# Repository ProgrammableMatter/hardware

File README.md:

Particle Hardware Repository
----------------------------
Hardware development repository for the particle and related hardware.

## Folder content
* **pcb-projects**: pcb projects
* **freecad**: 3D Models drawn with [FreeCAD](http://www.freecadweb.org/)
* **reflow**: reflow soldering logs, charts and helper

## PCB Projects/Versions
### Particle Version 1.21
|   |   |   |
|---|---|---|
|  |  |  |
| plugable particle with leads | pluggable particle | grid board illustartion |

### Particle version 1.1

|   |   |   | 
|---|---|---|
||||
| single particle | array example | array header |
|  | | | 
| array tail | | |

### Particle version 0.9
|   |
|---|
||
| chain example |

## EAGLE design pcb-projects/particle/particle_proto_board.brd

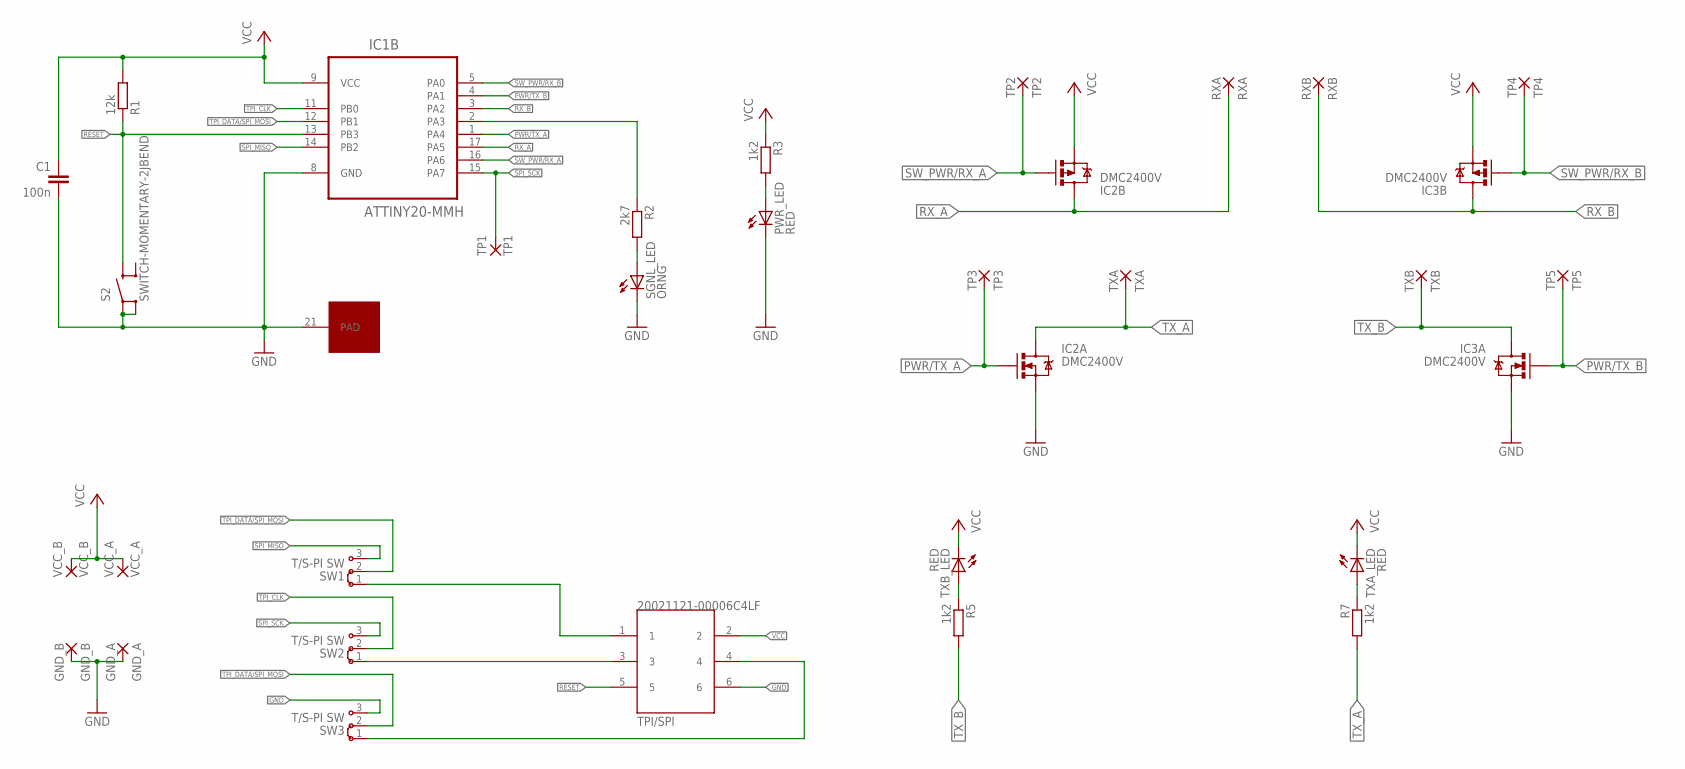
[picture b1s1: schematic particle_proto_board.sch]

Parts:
C1: 100n; C1206
GND_A: GND_A; 1,6/0,9
GND_B: GND_B; 1,6/0,9
IC1: ATTINY20-MMH; QFN45P300X300X85-21N
IC2, IC3: DMC2400V; SOT563
PWR_LED: RED; SML1206
R1: 12k; R1206
R2: 2k7; R1206
R3, R5, R7: 1k2; R1206
RXA: RXA; 1,6/0,9
RXB: RXB; 1,6/0,9
S2: SWITCH-MOMENTARY-2JBEND; KSC351JLFS
SGNL_LED: ORNG; SML1206
SW1, SW2, SW3: T/S-PI SW; 04C
TP1: TP1; 1,6/0,9
TP2: TP2; 1,6/0,9
TP3: TP3; 1,6/0,9
TP4: TP4; 1,6/0,9
TP5: TP5; 1,6/0,9
TPI/SPI: 20021121-00006C4LF
TXA: TXA; 1,6/0,9
TXA_LED: RED; SML1206
TXB: TXB; 1,6/0,9
TXB_LED: RED; SML1206
VCC_A: VCC_A; 1,6/0,9
VCC_B: VCC_B; 1,6/0,9

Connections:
GND: C1.2, GND_A.1, GND_B.1, IC1.8 (GND), IC1.21 (PAD), IC2.1 (S), IC3.1 (S), PWR_LED.C, S2.1@1 (1), S2.1@2 (1), SGNL_LED.C, SW3.3, TPI/SPI.6
unnamed: SW1.1, TPI/SPI.1
unnamed: SW3.1, TPI/SPI.4
unnamed: R7.1, TXA_LED.A
unnamed: SW2.1, TPI/SPI.3
unnamed: R5.1, TXB_LED.A
unnamed: R2.2, SGNL_LED.A
unnamed: PWR_LED.A, R3.2
unnamed: IC1.2 (PA3), R2.1
PWR/TX_A: IC1.1 (PA4), IC2.2 (G), TP3.1
PWR/TX_B: IC1.4 (PA1), IC3.2 (G), TP5.1
RESET: IC1.13 (PB3), R1.1, S2.2@1 (2), TPI/SPI.5
RX_A: IC1.17 (PA5), IC2.3 (D), RXA.1
RX_B: IC1.3 (PA2), IC3.3 (D), RXB.1
SPI_MISO: IC1.14 (PB2), SW1.3
SPI_SCK: IC1.15 (PA7), SW2.3, TP1.1
SW_PWR/RX_A: IC1.16 (PA6), IC2.5 (G), TP2.1
SW_PWR/RX_B: IC1.5 (PA0), IC3.5 (G), TP4.1
TPI_CLK: IC1.11 (PB0), SW2.2
TPI_DATA/SPI_MOSI: IC1.12 (PB1), SW1.2, SW3.2
TX_A: IC2.6 (D), R7.2, TXA.1
TX_B: IC3.6 (D), R5.2, TXB.1
VCC: C1.1, IC1.9 (VCC), IC2.4 (S), IC3.4 (S), R1.2, R3.1, TPI/SPI.2, TXA_LED.C, TXB_LED.C, VCC_A.1, VCC_B.1

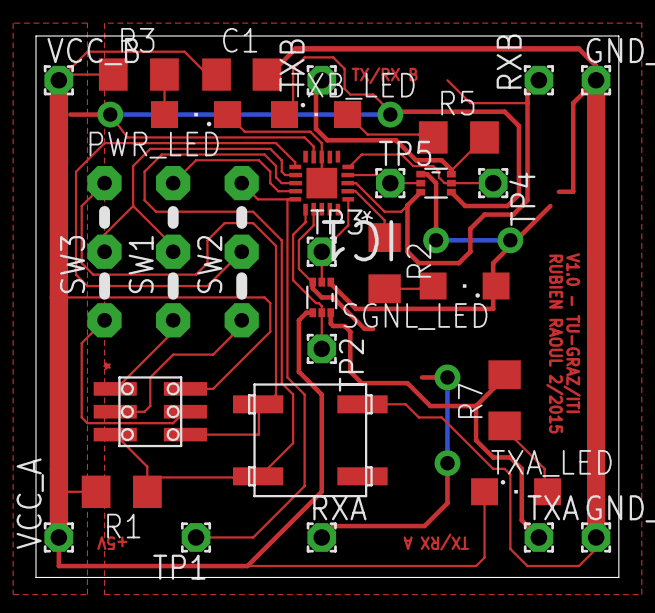
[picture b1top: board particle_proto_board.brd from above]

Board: 2 copper layers, 32.4 x 30.1 mm, 31 parts (0 on the bottom side), 23 nets.

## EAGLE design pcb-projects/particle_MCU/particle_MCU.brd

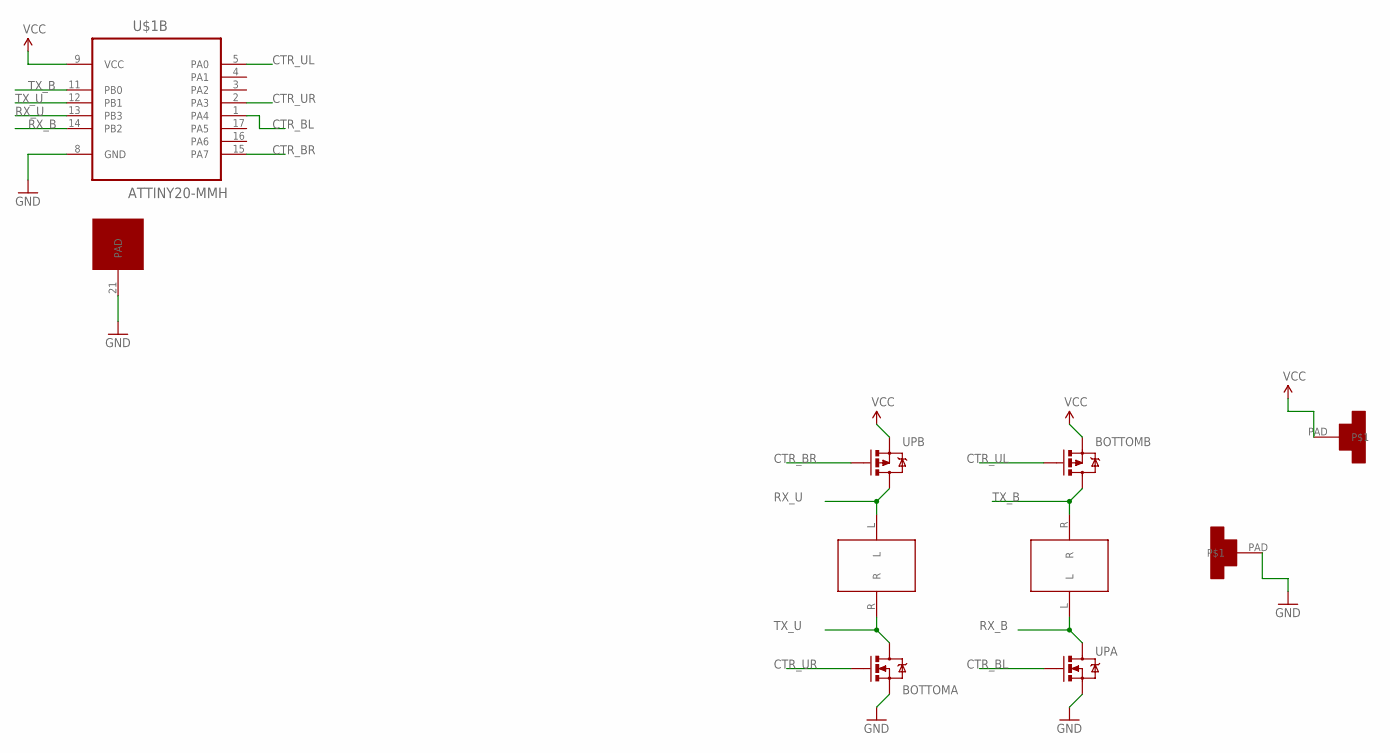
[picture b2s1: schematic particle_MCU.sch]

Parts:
BOTTOM: DMC2400V; SOT563
U$1: ATTINY20-MMH; QFN45P300X300X85-21N
U$2, U$5: EDGE_PAD; ROUND_EDGE_CONNECTOR
U$3, U$4: SMA-DUAL-CONN4MM; SMA_DOUBLE_PIN2_4MM
UP: DMC2400V; SOT563

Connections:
CTR_BL: U$1.1 (PA4), UP.2 (G)
CTR_BR: U$1.15 (PA7), UP.5 (G)
CTR_UL: BOTTOM.5 (G), U$1.5 (PA0)
CTR_UR: BOTTOM.2 (G), U$1.2 (PA3)
GND: BOTTOM.1 (S), U$1.8 (GND), U$1.21 (PAD), U$5.PAD, UP.1 (S)
RX_B: U$1.14 (PB2), U$4.L, UP.6 (D)
RX_U: U$1.13 (PB3), U$3.L, UP.3 (D)
TX_B: BOTTOM.3 (D), U$1.11 (PB0), U$4.R
TX_U: BOTTOM.6 (D), U$1.12 (PB1), U$3.R
VCC: BOTTOM.4 (S), U$1.9 (VCC), U$2.PAD, UP.4 (S)

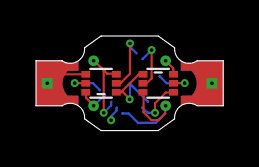
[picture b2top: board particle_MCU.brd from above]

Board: 4 copper layers, 10.4 x 5.3 mm, 7 parts (1 on the bottom side), 10 nets.

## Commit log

2015-01-15 added particle project
2015-01-19 added initial version of proto pcb
2015-01-20 close issue #4, close issue #8
2015-01-20 connected h-bridges to comm wires
2015-01-21 begun with tpi connector
2015-01-22 begun with routing
2015-01-23 added test pins
2015-01-23 routed bard
2015-01-23 added missing track and vcc/gnd holes
2015-01-26 replaced packages/library of attiny20 and dmc2400uv
2015-01-27 close 21, close 22
2015-01-27 fixes #13
2015-01-28 routing board
2015-01-29 close #26, close #31, close #30, close #28, close #25, close #24, close #23
2015-01-29 close #27, close #19, close #30,skip / close #18, skip / close #14
2015-01-31 renamed folder
2015-01-31 routed isp header
2015-01-31 routed board - usable version without filling in gnd/vcc fields
2015-01-31 fixed some issues, added polygons
2015-01-31 filled out vcc/gnd areas
2015-02-01 set values to all leds, renamed gnd/vcc pads, TX/RX description beside pads, placed vcc/gnd shunts exposed on schema
2015-02-01 renamed files/folder
2015-02-01 fixed typo in schema
2015-02-02 solved #34, solved #33, solved #32
2015-02-02 added several sparkfun and one samtec library, fixed #39, fixed #37, fixed #36, fixed #35, fixed #29
2015-02-03 fixed #41, fixed #40, fixed #39, fixed #37, fixed #35, fixed #29
2015-02-04 routed board after several changes to schema
2015-02-04 closed #44, closed #43, closed #42
2015-02-05 renamed parts in schema
2015-02-06 fixed #47
2015-02-08 corrected version number
2015-02-08 created library for several smt switches (rs components)
2015-02-09 routed board with rs components
2015-02-09 added missing wire
2015-02-09 cosmetics
2015-02-09 removed obsolet library folder
2015-02-10 changed 90° spi connector to straight one
2015-02-10 fixed wrong tpi/spi-switch configuration matrix on schema
2015-02-10 small modification
2015-02-10 changed all resistors 1k -> 150
2015-02-11 cosmetics: moved 5V label and testpoint 1 smome mm
2015-02-11 enhanced switch: now has 4 terminals - polygon filling now makes termal pad correct
2015-02-12 successfully connected four tiny airwires below pads
2015-02-12 last updates
2015-02-12 reduced size
2015-02-12 aligned C1
2015-02-12 tstop polygon
2015-02-19 added script for connecting and logging the reflow controller
2015-02-19 created a reflow profile for the tug oven
2015-02-20 ignoring eagle leftovers
2015-02-20 removed unnecessary file
2015-02-25 highlighted design error on schema regarding tx-leds
2015-03-01 fixed #52, fixed #53, fixed #54, fixed #57
2015-05-05 soldering oven heat curves
2015-09-28 added reflow temperature curves
2015-12-22 removed led on rx due to damping signal issue
2016-01-04 added particle sketch created with kicad
2016-01-04 deleted temp files
2016-01-04 routed attiny1634 particle
2016-01-06 re-routed smaller pcb, added several 3d packages, min. fix in schema
2016-01-06 added all 3d models, pcb cosmetics
2016-01-06 increased clearance from 0.2mm to 0.33mm
2016-01-08 added bill of material
2016-01-09 added usb connector module/3d
2016-01-10 added border to usb footprint
2016-01-10 added array header and tail
2016-01-10 removed bak files
2016-01-27 minor edge cut alignment, added particle array
2016-01-28 routed pluggable particle
2016-01-29 added board with lead
2016-01-30 run cleaned up on pcbs
2016-01-30 added euro-pcb with multiple modules placed on it
2016-01-31 remved no-net zones, refined gnd zone
2016-01-31 added power supply capacitor
2016-01-31 updated euro pcb
2016-02-01 minor change: updated MCU power supply decoupling and euro pcb
2016-02-03 removed mistakenly exported grid planes
2016-02-03 elongated leads
2016-02-03 added grid board visualization
2016-02-03 added mosfet-sma-connection example schema
2016-02-04 added grid board sketch
2016-02-04 refined grid board: cutouts
2016-02-04 restructured folder hierarchy
2016-02-04 change shape, updated euro pcb
2016-02-04 added missing symlinks
2016-02-04 updated grid board sketch
2016-02-08 grid board illustration is now in grey
2016-02-08 added particle v1.1 array
2016-07-20 changed network names slightly
2016-08-03 cleanup folders; minimal pcb changes
2016-08-03 removed redundant files
2016-08-03 renamed files
2016-08-03 removed file
2016-08-03 added readme
2016-08-03 added more images
2016-08-07 restored tx bridge example schema

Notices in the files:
parts and their libraries:
SparkFun: Licensing: CC v3.0 Share-Alike You are welcome to use this library for commercial purposes.
